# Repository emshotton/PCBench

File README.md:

# PCBench: A Dataset for Printed Circuit Board Routing
PCBench is a dataset for PCB routing task, it includes a dataset consisting of 164 printed circuit boards (PCB), a data augmentation script  to expand the dataset for supervised learning (SL) tasks, and a reinforcement learning (RL) environment.

## Dataset
### Folder Structure
All the PCB designs in our dataset are stored in the folder `PCBs`, where each PCB design is stored in a subfolder named `{author/org}_{PCB_name}_{design_version(optional)}`. Below is the folder structure of the dataset.
```
├── PCBs
│   ├── master_metadata.json
│   ├── subfolder1
│   │   ├── raw.kicad_pcb
│   │   ├── processed.kicad_pcb
│   │   ├── final.json
│   │   ├── metadata.json
│   │   ├── visual.png
│   ├── subfolder2
│   │   ├── raw.kicad_pcb
│   │   ├── processed.kicad_pcb
│   │   ├── final.json
│   │   ├── metadata.json
│   │   ├── visual.png
│   ├── ...
```
The `raw.kicad_pcb` is the raw PCB design file, `process.kicad_pcb` is the file after cleaning up, `final.json` stores only  routing-related information used for ML tasks. `metadata.json` stores the meta information for each single PCB design. `visual.png` is a visualization of each single PCB design. `master_meta.json` contains metadata of all PCBs and global-level information.

### PCB Routing Description Language (PCB-RDL)
We propose a JSON specification (`final.json` for each PCB design) called the PCB Routing Description  Language (PCB-RDL) that expresses a PCB routing problem and its solutions intuitively using basic concepts in order to facilitate research into automated PCB routing using ML. Following figure shows is an example of PCB with marked components in PCB-RDL (Left) and it corrsponding PCB-RDL (Right).

## Data Augmentation
### Run
The augmentation data can be generated with the script [`Scripts/Data_augmentation/augmentation.py`](https://github.com/PCBench/PCBench/blob/main/Scripts/Data_augmentation/augmentation.py).  To generate 3 samples by randomly extracting 50% nets from the PCB `1Bitsy_1bitsy`, please run the following command
```
cd Scripts/Data_augmentation/
python augmentation.py --num_samples 3 --net_ratio 0.5 --pcb_name 1Bitsy_1bitsy
```
### Output
All the generated PCBs will be stored in the folder named `augmented_data` under  `Scripts/Data_augmentation/`. In `augmented_data`, all the generated samples will be stored in a subfolder with the name of selected PCB. Each generated sample has the name `sample_index.json`. For example, the above command will generate the following file under `Scripts/Data_augmentation/`
```
├── augmented_data
│   ├── 1Bitsy_1bitsy
│   │   ├── 1.json
│   │   ├── 2.json
│   │   ├── 3.json
```

## RL environment

### Installation
The RL environment requires Python >= 3.7. You can simply install the environment with the following commands:
```
git clone https://github.com/PCBench/PCBench.git
cd PCBench
python setup.py install
```
After installation, open a Python console and type
```
from RLEnv.EnvLayer.PCBRoutingEnv import PCBRoutingEnv
```
If no error occurs, you have successfully installed the PCB routing environment.

### API Usage
The following content shows an example of API usage of PCBRoutingEnv. 
```
from RLEnv.EnvLayer.PCBRoutingEnv import PCBRoutingEnv
import random

resolution = [0.5, 0.5]
pcb_folder = '../PCBs/'
pcb_names = ["1Bitsy_1bitsy"]
iters = 30
env = PCBRoutingEnv(resolution=resolution, pcb_folder=pcb_folder, pcb_names=pcb_names)
obs, info = env.reset()
for _ in range(iters):
    act = random.randint(0,5)
    obs, rew, terminal, _, info = env.step(act)
    if terminal:
        env.reset()
```
You can find more examples of customizing functions of reward and state observation from [RLEnv/examples.ipynb](https://github.com/PCBench/PCBench/blob/main/RLEnv/examples.ipynb).

## Licensing

The code in this repository (scripts, the RL environment, notebooks) is released under the
MIT license in [`LICENSE`](LICENSE). **The boards under `PCBs/` are not.** Each board keeps
the license its authors chose, and each board folder records it:

- `metadata.json` → `licenses` holds the SPDX id, the license file's path in the source
  repository, the source commit the board was taken from, and a `status`:
  `licensed`, `licensed-unclassified` (a license file exists but could not be reduced to one
  SPDX id; read it), `unlicensed` (the source publishes no license), or `source-missing`
  (the source repository has since been deleted).
- `LICENSE` is the license text copied verbatim from the source repository.
- `NOTICE.md` carries the attribution (author, source, commit, retrieval date) and the
  modification statement required by CERN-OHL, the GPL family and the Creative Commons
  licenses: `processed.kicad_pcb` and `final.json` are derived from `raw.kicad_pcb` and stay
  under the source license.

Boards marked `unlicensed` are held for research and evaluation only. Their authors retain
all rights, and they must not be redistributed; [`LICENSES.md`](LICENSES.md) lists them
along with counts per license. `Scripts/Licensing/resolve_licenses.py` regenerates all of
the above from the source repositories.

### Boards added after the original collection

Boards added with `Scripts/Data_collection/add_boards.py` (their `metadata.json` carries
`source_path` and `source_commit`) differ from the original 1182 in two ways:
`processed.kicad_pcb` is the raw board with zone fills removed and routing kept, rather than
the re-routed board of the original cleaning pipeline; and `final.json`/`visual.png` are not
present, because the PCB-RDL extractor handles the KiCad 5 file format only.

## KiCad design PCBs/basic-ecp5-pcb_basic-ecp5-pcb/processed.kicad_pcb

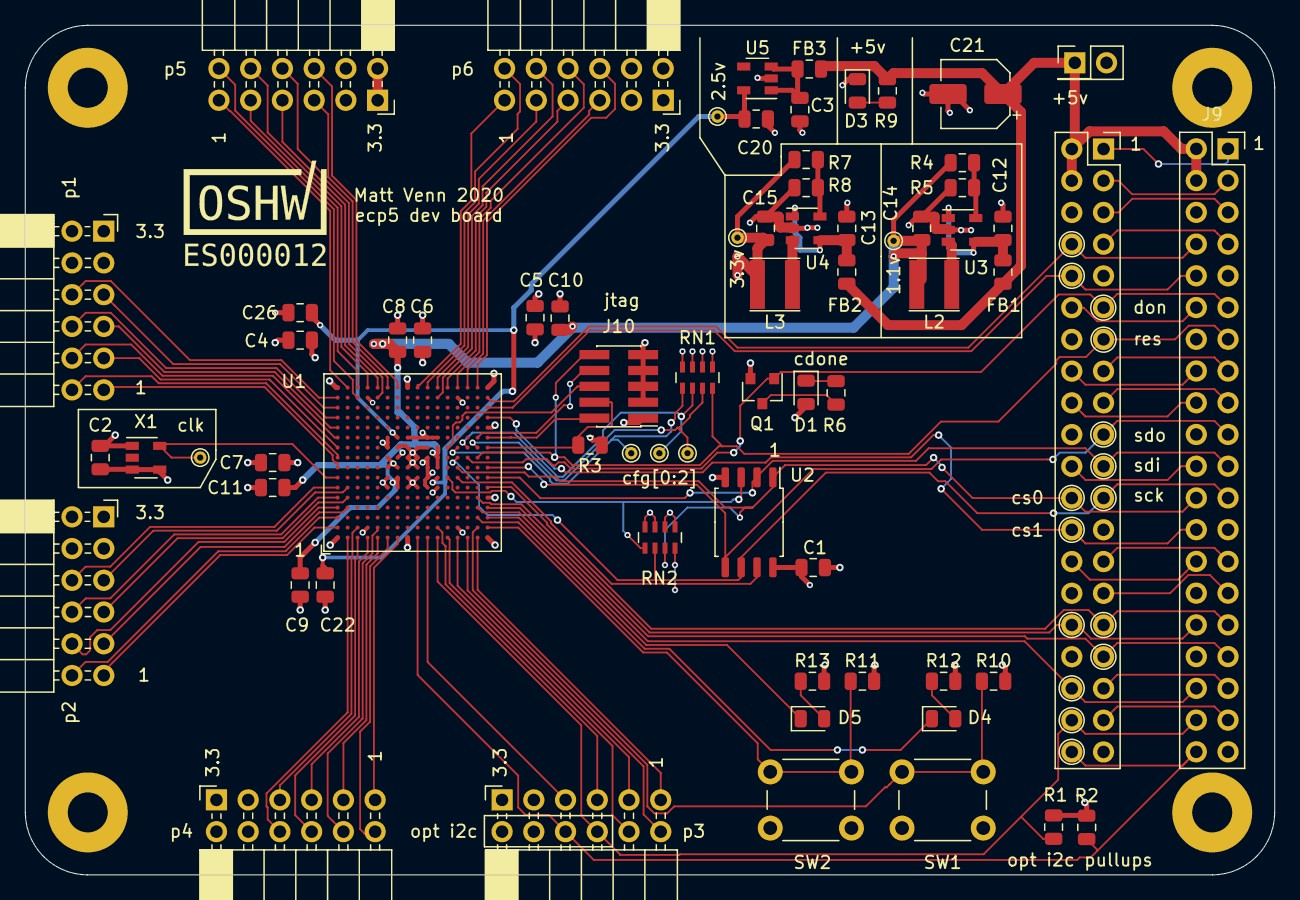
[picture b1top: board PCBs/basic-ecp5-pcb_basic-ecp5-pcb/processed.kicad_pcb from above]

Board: 4 copper layers, 100.0 x 68.0 mm, 73 parts (0 on the bottom side), 107 nets.

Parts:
C1, C2, C4, C5, C6, C8, C9, C10, C22: 100n; C_0805_2012Metric
C3, C20: 1u; C_0805_2012Metric
C7, C11, C15, C26: 10u; C_0805_2012Metric
C12, C13: 4.7u; C_0805_2012Metric
C14: 22u; C_0805_2012Metric
C21: CP; CP_Elec_5x5.4
D1, D3, D4, D5: LED; LED_0805_2012Metric
FB1, FB2, FB3: Ferrite_Bead_Small; L_0805_2012Metric
H1, H2, H3, H4: MountingHole_Pad; MountingHole_3.2mm_M3_Pad
J1: Conn_01x02; PinHeader_2x01_P2.54mm_Vertical
J2, J9: Conn_02x20_Odd_Even; PinSocket_2x20_P2.54mm_Vertical
J3, J4, J5, J6, J7, J8: Conn_02x06_Odd_Even; PinSocket_2x06_P2.54mm_Horizontal
J10: Conn_02x05_Odd_Even; PinHeader_2x05_P1.27mm_Vertical_SMD
L2, L3: 2.2uH; L_Taiyo-Yuden_NR-40xx
Q1: Q_NMOS_GSD; SOT-23
R1, R2, R3, R10, R11: 10k; R_0805_2012Metric
R4: 100k; R_0805_2012Metric
R5: 120k; R_0805_2012Metric
R6, R9, R12, R13: 200R; R_0805_2012Metric
R7: 68k; R_0805_2012Metric
R8: 15k; R_0805_2012Metric
RN1, RN2: 10k; R_Array_Concave_4x0603
SW1, SW2: SW_Push; SW_PUSH_6mm
TP1: 3.3v; TestPoint_THTPad_D1.0mm_Drill0.5mm
TP2, TP4, TP7: TestPoint; TestPoint_THTPad_D1.0mm_Drill0.5mm
TP3: 2.5v; TestPoint_THTPad_D1.0mm_Drill0.5mm
TP5: clock; TestPoint_THTPad_D1.0mm_Drill0.5mm
TP6: 1.1v; TestPoint_THTPad_D1.0mm_Drill0.5mm
U1: ECP5U_45_CABGA256; BGA-256_14.0x14.0mm_Layout16x16_P0.8mm_Ball0.45mm_Pad0.32mm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
U2: IS25LP016D-JBLE; SOIC-8_5.23x5.23mm_P1.27mm
U3, U4: TLV62568DBV; SOT-23-5
U5: TLV73325PDBV; SOT-23-5
X1: SiT2001B; SOT-23-5

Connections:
+1V1: C8.1, C9.1, C10.1, C11.1, C14.1, L2.2, R4.2, TP6.1, U1.G6, U1.G7, U1.G9, U1.L8, U1.L9, U1.L10
+2V5: C20.1, C22.1, C26.1, TP3.1, U1.G11, U1.L7, U5.5
+3.3VP: C1.1, C2.1, C4.1, C5.1, C6.1, C7.1, C15.1, D1.2, J3.1, J3.2, J4.1, J4.2, J5.1, J5.2, J6.1, J6.2, J7.1, J7.2, J8.1, J8.2, J10.1, L3.2, R1.1, R2.1, R7.2, R10.2, R11.2, R12.2, R13.2, RN1.5, RN1.7, RN2.5, RN2.6, RN2.7, RN2.8, TP1.1, U1.F6, U1.F7, U1.F10, U1.F11, U1.H6, U1.H7, U1.H11, U1.J6, U1.J7, U1.J11, U1.K11, U1.L6, U1.L11, U2.8, X1.3, X1.4
+5V: C21.1, FB1.2, FB2.2, FB3.2, J1.1, J2.2, J2.4, J9.2, J9.4, R9.2
/fpga/cfg_0: RN1.1, TP2.1, U1.N10
/fpga/cfg_1: RN1.2, TP4.1, U1.P10
/fpga/cfg_2: RN1.3, TP7.1, U1.R10
/fpga/tck: J10.4, R3.2, U1.T10
/fpga/tdi: J10.8, U1.R11
/fpga/tdo: J10.6, U1.M10
/fpga/tms: J10.2, U1.T11
/gp0: J2.27, J9.27
/gp1: J2.28, J9.28
/gp2: J2.3, J9.3
/gp3: J2.5, J9.5
/gp4: J2.7, J9.7
/gp5: J2.29, J9.29
/gp18: J2.12, J9.12
/gp19: J2.35, J9.35
/gp22: J2.15, J9.15
/gp23: J2.16, J9.16
/gp24: J2.18, J9.18
/gp25: J2.22, J9.22
/gp26: J2.37, J9.37
/pi_3v3: J2.1, J9.1
/pi_3v3_2: J2.17, J9.17
GND: C1.2, C2.2, C3.2, C4.2, C5.2, C6.2, C7.2, C8.2, C9.2, C10.2, C11.2, C12.2, C13.2, C14.2, C15.2, C20.2, C21.2, C22.2, C26.2, D3.1, H1.1, H2.1, H3.1, H4.1, J1.2, J2.6, J2.9, J2.14, J2.20, J2.25, J2.30, J2.34, J2.39, J3.3, J3.4, J4.3, J4.4, J5.3, J5.4, J6.3, J6.4, J7.3, J7.4, J8.3, J8.4, J9.6, J9.9, J9.14, J9.20, J9.25, J9.30, J9.34, J9.39, J10.3, J10.5, J10.7, J10.9, Q1.2, R3.1, R5.1, R8.1, RN1.6, RN1.8, SW1.2, SW2.2, U1.A1, U1.A16, U1.D2, U1.D15, U1.F8, U1.F9, U1.G8, U1.G10, U1.H1, U1.H8, U1.H9, U1.H10, U1.H16, U1.J8, U1.J9, U1.J10, U1.K6, U1.K7, U1.K8, U1.K9, U1.K10, U1.N2, U1.N15, U1.T1, U1.T5, U1.T12, U1.T16, U2.4, U3.2, U4.2, U5.2, X1.1
unnamed: C3.1, FB3.1, U5.1, U5.3
unnamed: C12.1, FB1.1, U3.1, U3.4
unnamed: C13.1, FB2.1, U4.1, U4.4
unnamed: D1.1, R6.1
unnamed: D3.2, R9.1
unnamed: D4.2, R12.1
unnamed: D5.2, R13.1
unnamed: L2.1, U3.3
unnamed: L3.1, U4.3
unnamed: Q1.3, R6.2
unnamed: R4.1, R5.2, U3.5
unnamed: R7.1, R8.2, U4.5
button1: R10.1, SW1.1, U1.R2
button2: R11.1, SW2.1, U1.T2
cdone: J2.11, J9.11, Q1.1, U1.P9
ce1: J2.26, J9.26, U1.T13
clk: TP5.1, U1.A7, X1.5
creset: J2.13, J9.13, J10.10, RN1.4, U1.R9
gp6: J2.31, J9.31, U1.T6
gp12: J2.32, J9.32, U1.R5
gp13: J2.33, J9.33, U1.T4
gp14: J2.8, J9.8, U1.T15
gp15: J2.10, J9.10, U1.T14
gp16: J2.36, J9.36, U1.R4
led1: D4.1, U1.R3
led2: D5.1, U1.T3
p1_1: J3.11, U1.A8
p1_2: J3.9, U1.A10
p1_3: J3.7, U1.A12
p1_4: J3.5, U1.A14
p1_7: J3.12, U1.A9
p1_8: J3.10, U1.A11
p1_9: J3.8, U1.A13
p1_10: J3.6, U1.A15
p2_1: J4.11, U1.A2
p2_2: J4.9, U1.B4
p2_3: J4.7, U1.B5
p2_4: J4.5, U1.B6
p2_7: J4.12, U1.A3
p2_8: J4.10, U1.A4
p2_9: J4.8, U1.A5
p2_10: J4.6, U1.A6
p3_1: J5.11, U1.R1
p3_2: J5.9, U1.N1
p3_3: J5.7, U1.L2
p3_4: J5.5, U1.K1
p3_7: J5.12, U1.P1
p3_8: J5.10, U1.M1
p3_9: J2.38, J5.8, J9.38, R1.2, U1.L1
p3_10: J2.40, J5.6, J9.40, R2.2, U1.J1
p4_1: J6.11, U1.G1
p4_2: J6.9, U1.E1
p4_3: J6.7, U1.D1
p4_4: J6.5, U1.C2
p4_7: J6.12, U1.F1
p4_8: J6.10, U1.E2
p4_9: J6.8, U1.C1
p4_10: J6.6, U1.B1
p5_1: J7.11, U1.B16
p5_2: J7.9, U1.C16
p5_3: J7.7, U1.E16
p5_4: J7.5, U1.F16
p5_7: J7.12, U1.C15
p5_8: J7.10, U1.D16
p5_9: J7.8, U1.E15
p5_10: J7.6, U1.G16
p6_1: J8.11, U1.J16
p6_2: J8.9, U1.L16
p6_3: J8.7, U1.M16
p6_4: J8.5, U1.P16
p6_7: J8.12, U1.K16
p6_8: J8.10, U1.L15
p6_9: J8.8, U1.N16
p6_10: J8.6, U1.R16
sd_clk: J2.23, J9.23, RN2.2, U1.N9, U2.6
sd_cs: J2.24, J9.24, RN2.3, U1.N8, U2.1
sd_io2: RN2.1, U1.M7, U2.3
sd_io3: RN2.4, U1.N7, U2.7
sdi: J2.21, J9.21, U1.T7, U2.2
sdo: J2.19, J9.19, U1.T8, U2.5

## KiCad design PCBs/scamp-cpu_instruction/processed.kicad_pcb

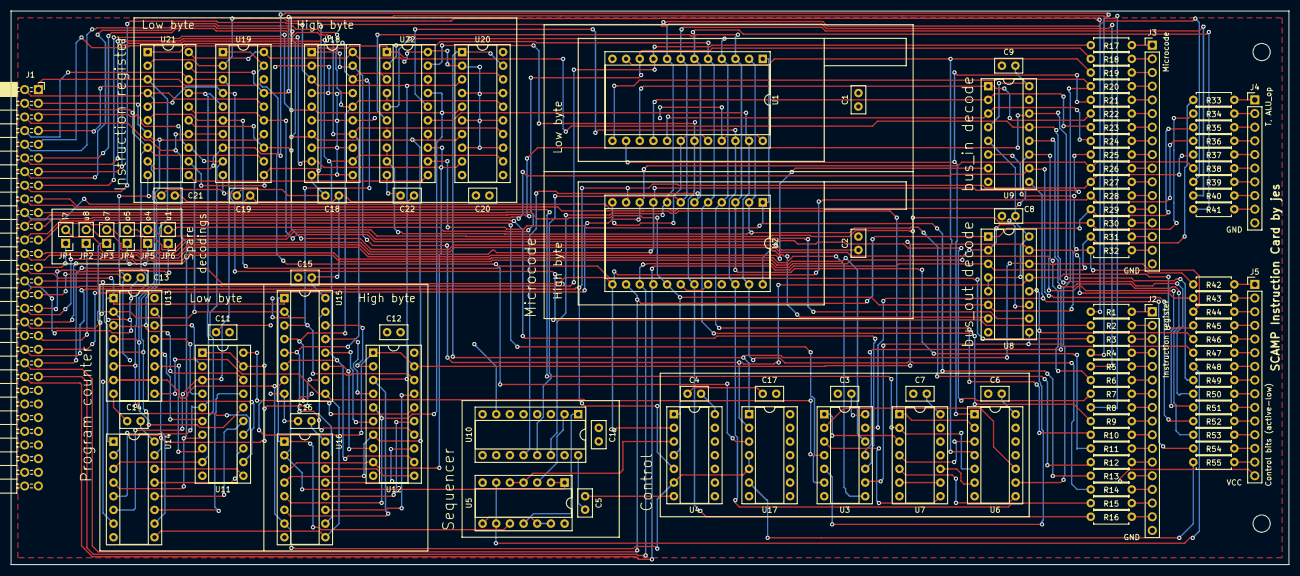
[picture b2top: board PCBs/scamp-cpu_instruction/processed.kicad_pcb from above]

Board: 2 copper layers, 237.5 x 102.9 mm, 110 parts (0 on the bottom side), 172 nets.

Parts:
C1, C2, C3, C4, C5, C6, C7, C8, C9, C10, C11, C12, C13, C14, C15, C16, C17, C18, C19, C20, C21, C22: C; C_Disc_D5.0mm_W2.5mm_P2.50mm
J1: Conn_02x30_Counter_Clockwise; PinSocket_2x30_P2.54mm_Horizontal
J2, J3: Conn_01x17_Male; PinHeader_1x17_P2.54mm_Vertical
J4: Conn_01x10_Male; PinHeader_1x10_P2.54mm_Vertical
J5: Conn_01x15_Male; PinHeader_1x15_P2.54mm_Vertical
JP1, JP2, JP3, JP4, JP5, JP6: Jumper_NO_Small; PinHeader_1x02_P2.54mm_Vertical
R1, R2, R3, R4, R5, R6, R7, R8, R9, R10, R11, R12, R13, R14, R15, R16, R17, R18, R19, R20, R21, R22, R23, R24, R25, R26, R27, R28, R29, R30, R31, R32, R33, R34, R35, R36, R37, R38, R39, R40, R41, R42, R43, R44, R45, R46, R47, R48, R49, R50, R51, R52, R53, R54, R55: R; R_Axial_DIN0207_L6.3mm_D2.5mm_P7.62mm_Horizontal
U1, U2: 28C16; DIP-24_W15.24mm_Socket
U3: 74LS04; DIP-14_W7.62mm_Socket
U4, U6: 74LS08; DIP-14_W7.62mm_Socket
U5, U17: 74LS00; DIP-14_W7.62mm_Socket
U7: 74LS32; DIP-14_W7.62mm_Socket
U8, U9: 74LS138; DIP-16_W7.62mm_Socket
U10, U13, U14, U15, U16: 74LS161; DIP-16_W7.62mm_Socket
U11, U12, U18, U19, U20: 74LS244; DIP-20_W7.62mm_Socket
U21, U22: 74LS377; DIP-20_W7.62mm_Socket

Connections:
CLK: J1.29, U5.1, U5.2, U13.2, U14.2, U15.2, U16.2, U21.11, U22.11
D0: J1.1, U11.18, U13.3, U19.18, U21.3
D1: J1.2, U11.16, U13.4, U19.16, U21.4
D2: J1.3, U11.14, U13.5, U19.14, U21.7
D3: J1.4, U11.12, U13.6, U19.12, U21.8
D4: J1.5, U11.9, U14.3, U19.9, U21.13
D5: J1.6, U11.7, U14.4, U19.7, U21.14
D6: J1.7, U11.5, U14.5, U19.5, U21.17
D7: J1.8, U11.3, U14.6, U19.3, U21.18
D8: J1.9, U12.18, U15.3, U18.18, U20.18, U22.3
D9: J1.10, U12.16, U15.4, U18.16, U20.16, U22.4
D10: J1.11, U12.14, U15.5, U18.14, U20.14, U22.7
D11: J1.12, U12.12, U15.6, U18.12, U20.12, U22.8
D12: J1.13, U12.9, U16.3, U18.9, U20.9, U22.13
D13: J1.14, U12.7, U16.4, U18.7, U20.7, U22.14
D14: J1.15, U12.5, U16.5, U18.5, U20.5, U22.17
D15: J1.16, U12.3, U16.6, U18.3, U20.3, U22.18
DI: J1.26, U3.12
DO: J1.25, U3.8
EX: J1.44, R31.1, R33.1, U2.16, U8.3
EY: J1.42, R29.1, R35.1, U2.14, U8.1
F: J1.40, R27.1, R37.1, U2.11, U4.5
GND: C1.2, C2.2, C3.2, C4.2, C5.2, C6.2, C7.2, C8.2, C9.2, C10.2, C11.2, C12.2, C13.2, C14.2, C15.2, C16.2, C17.2, C18.2, C19.2, C20.2, C21.2, C22.2, J1.31, J2.17, J3.17, J4.10, U1.12, U1.18, U1.20, U2.12, U2.18, U2.20, U3.7, U4.7, U5.7, U6.7, U7.7, U8.8, U9.8, U10.8, U11.10, U12.10, U13.8, U14.8, U15.8, U16.8, U17.7, U18.2, U18.4, U18.6, U18.8, U18.10, U18.11, U18.13, U18.15, U18.17, U19.10, U20.10, U21.10, U22.10
GT: U3.2, U6.10
I0: R1.1, U19.2, U21.2
I1: R2.1, U19.4, U21.5
I2: R3.1, U19.6, U21.6
I3: R4.1, U19.8, U21.9
I4: R5.1, U19.11, U21.12
I5: R6.1, U19.13, U21.15
I6: R7.1, U19.15, U21.16
I7: R8.1, U19.17, U21.19
I8: R9.1, U1.5, U2.5, U22.2
I9: R10.1, U1.4, U2.4, U22.5
I10: R11.1, U1.3, U2.3, U22.6
I11: R12.1, U1.2, U2.2, U22.9
I12: R13.1, U1.1, U2.1, U22.12
I13: R14.1, U1.23, U2.23, U22.15
I14: R15.1, U1.22, U2.22, U22.16
I15: R16.1, U1.19, U2.19, U22.19
JGT: R20.1, U1.13, U6.9
JGT_GT: U6.8, U7.5
JLT: R19.1, U1.11, U6.4
JLT_LT: U6.6, U7.10
JMP: U3.3, U7.8
JZ: R21.1, U1.14, U6.1
JZ_Z: U6.3, U7.4
LT: J1.18, U6.5, U7.2
MI: J1.24, U3.10
MO: J1.23, U3.6
NO: J1.39, R26.1, R38.1, U2.10
NX: J1.43, R30.1, R34.1, U2.15, U8.2
NY: J1.41, R28.1, R36.1, U2.13, U4.2
unnamed: J1.27, JP1.1
unnamed: J1.33, JP6.1
unnamed: J1.34, JP5.1
unnamed: J1.35, JP4.1
unnamed: J1.36, JP3.1
unnamed: J1.37, JP2.1
unnamed: J2.1, R1.2
unnamed: J2.2, R2.2
unnamed: J2.3, R3.2
unnamed: J2.4, R4.2
unnamed: J2.5, R5.2
unnamed: J2.6, R6.2
unnamed: J2.7, R7.2
unnamed: J2.8, R8.2
unnamed: J2.9, R9.2
unnamed: J2.10, R10.2
unnamed: J2.11, R11.2
unnamed: J2.12, R12.2
unnamed: J2.13, R13.2
unnamed: J2.14, R14.2
unnamed: J2.15, R15.2
unnamed: J2.16, R16.2
unnamed: J3.1, R17.2
unnamed: J3.2, R18.2
unnamed: J3.3, R19.2
unnamed: J3.4, R20.2
unnamed: J3.5, R21.2
unnamed: J3.6, R22.2
unnamed: J3.7, R23.2
unnamed: J3.8, R24.2
unnamed: J3.9, R25.2
unnamed: J3.10, R26.2
unnamed: J3.11, R27.2
unnamed: J3.12, R28.2
unnamed: J3.13, R29.2
unnamed: J3.14, R30.2
unnamed: J3.15, R31.2
unnamed: J3.16, R32.2
unnamed: J4.1, R33.2
unnamed: J4.2, R34.2
unnamed: J4.3, R35.2
unnamed: J4.4, R36.2
unnamed: J4.5, R37.2
unnamed: J4.6, R38.2
unnamed: J4.7, R39.2
unnamed: J4.8, R40.2
unnamed: J4.9, R41.2
unnamed: J5.1, R42.2
unnamed: J5.2, R43.2
unnamed: J5.3, R44.2
unnamed: J5.4, R45.2
unnamed: J5.5, R46.2
unnamed: J5.6, R47.2
unnamed: J5.7, R48.2
unnamed: J5.8, R49.2
unnamed: J5.9, R50.2
unnamed: J5.10, R51.2
unnamed: J5.11, R52.2
unnamed: J5.12, R53.2
unnamed: J5.13, R54.2
unnamed: J5.14, R55.2
unnamed: U5.8, U5.12, U5.13
unnamed: U7.6, U7.9
unnamed: U13.15, U14.10
unnamed: U14.15, U15.10
unnamed: U15.15, U16.10
P0: U11.2, U13.14
P1: U11.4, U13.13
P2: U11.6, U13.12
P3: U11.8, U13.11
P4: U11.11, U14.14
P5: U11.13, U14.13
P6: U11.15, U14.12
P7: U11.17, U14.11
P8: U12.2, U15.14
P9: U12.4, U15.13
P10: U12.6, U15.12
P11: U12.8, U15.11
P12: U12.11, U16.14
P13: U12.13, U16.13
P14: U12.15, U16.12
P15: U12.17, U16.11
PP: U4.6, U13.7, U13.10, U14.7, U15.7, U16.7, U17.4, U17.5
RT: U4.3, U5.4, U5.5
T0: R39.1, U1.8, U2.8, U10.14
T1: R40.1, U1.7, U2.7, U10.13
T2: R41.1, U1.6, U2.6, U10.12
U0: J1.32, R17.1, U1.9
U1: JP6.2, R18.1, U1.10
U5: R22.1, U1.15, U9.1
U6: R23.1, U1.16, U9.2
U7: R24.1, U1.17, U9.3
U8: JP2.2, R25.1, U2.9
U15: J1.19, R32.1, R42.1, U2.17, U4.1, U4.4, U8.6, U9.6
VCC: C1.1, C2.1, C3.1, C4.1, C5.1, C6.1, C7.1, C8.1, C9.1, C10.1, C11.1, C12.1, C13.1, C14.1, C15.1, C16.1, C17.1, C18.1, C19.1, C20.1, C21.1, C22.1, J1.30, J5.15, U1.21, U1.24, U2.21, U2.24, U3.14, U4.14, U5.14, U6.14, U7.14, U8.4, U8.5, U8.16, U9.4, U9.5, U9.16, U10.7, U10.9, U10.10, U10.16, U11.20, U12.20, U13.16, U14.16, U15.16, U16.16, U17.14, U18.20, U19.20, U20.2, U20.4, U20.6, U20.8, U20.11, U20.13, U20.15, U20.17, U20.20, U21.20, U22.20
Z: J1.17, U6.2, U7.1
Z_LT: U3.1, U7.3
inv_CLK: U5.3, U10.2
inv_DI: R54.1, U3.13, U9.9
inv_DO: R47.1, U3.9, U8.9
inv_MI: R53.1, U3.11, U9.12
inv_MO: R46.1, U3.5, U8.12
inv_PP: R55.1, U17.6
inv_RT: R48.1, U5.6, U5.9
spare_I7: JP1.2, U9.7
spare_O4: JP5.2, U8.11
spare_O5: JP4.2, U8.10
spare_O7: JP3.2, U8.7
~AI~: J1.22, R49.1, U9.14
~II~: R50.1, U9.13, U21.1, U22.1
~IOH~: R44.1, U8.14, U17.1, U20.1, U20.19
~IOLH~: U17.3, U19.1, U19.19
~IOL~: R45.1, U8.13, U17.2, U18.1, U18.19
~JMP~: U3.4, U13.9, U14.9, U15.9, U16.9
~PO~: R43.1, U8.15, U11.1, U11.19, U12.1, U12.19
~RESET~: J1.28, U5.10, U13.1, U14.1, U15.1, U16.1
~XI~: J1.20, R51.1, U9.11
~YI~: J1.21, R52.1, U9.10
~reset_T~: U5.11, U10.1

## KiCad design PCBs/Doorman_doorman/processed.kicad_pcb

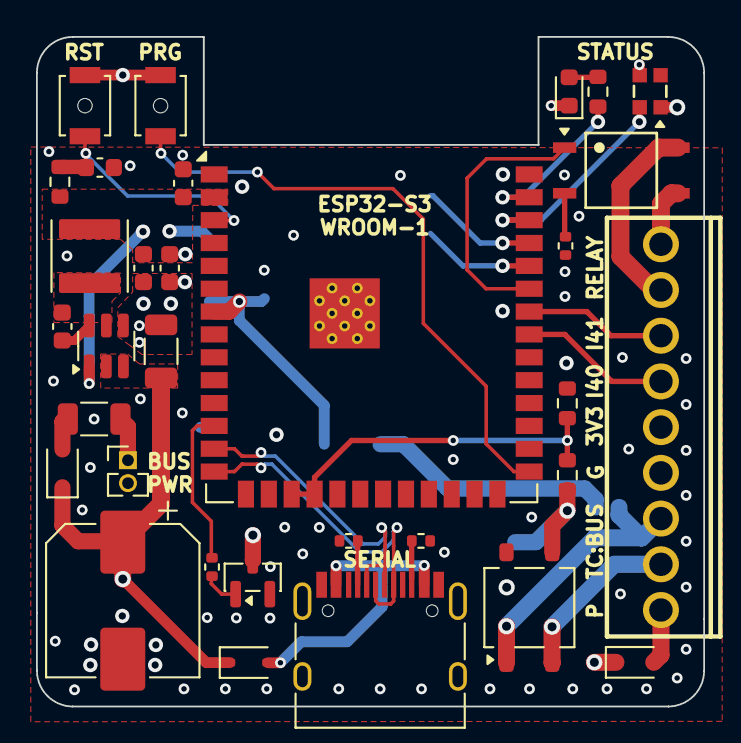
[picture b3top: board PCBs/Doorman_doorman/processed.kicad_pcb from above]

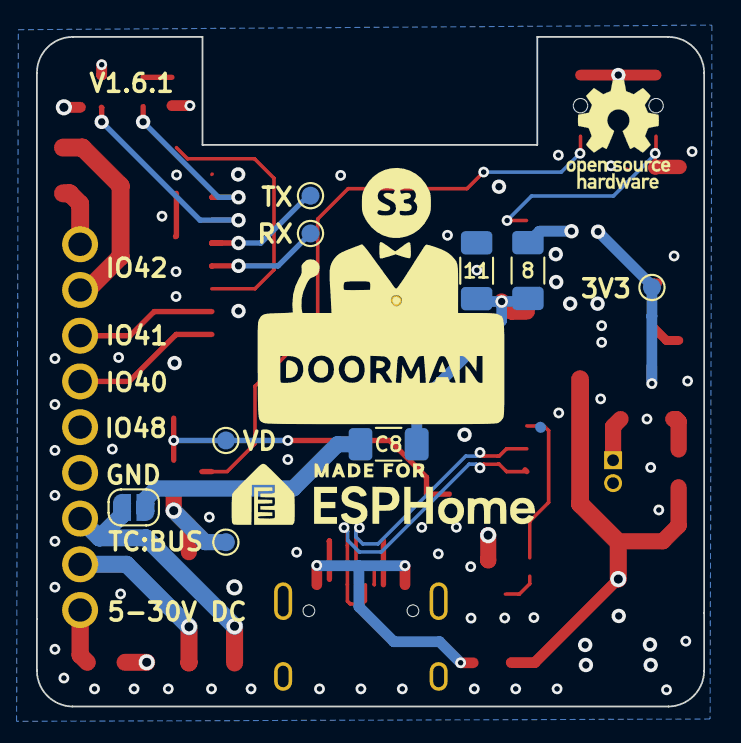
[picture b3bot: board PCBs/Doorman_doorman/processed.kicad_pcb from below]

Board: 4 copper layers, 37.1 x 37.2 mm, 41 parts (9 on the bottom side), 34 nets.

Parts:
8, 11: 10K; R_1206_3216Metric_Pad1.30x1.75mm_HandSolder
C1, C2, C5: 100nF; C_0603_1608Metric
C3: 470uF; CP_Elec_8x10
C4: 10uF; C_1206_3216Metric
C6, C7: 22uF; C_0603_1608Metric
C8: 33uF; C_1206_3216Metric_Pad1.33x1.80mm_HandSolder
D1, D5, D6: 1N5819WS; D_SOD-323
D2: MB6S; TO-269AA
D3: WS2812B; LED-SMD_4P-L2.0-W1.8_CY-0807
D4: Red; LED_0603_1608Metric
J1: USB_C_Receptacle_USB2.0; USB_C_Receptacle_HRO_TYPE-C-31-M-12
J2: Terminal; CONN-TH_9P-P2.54_KF128-2.54-9P
J3: 3V3 Test Pad; TestPoint_Pad_D1.0mm
J4: TX Test Pad; TestPoint_Pad_D1.0mm
J5: RX Test Pad; TestPoint_Pad_D1.0mm
J6: BUS Test Pad; TestPoint_Pad_D1.0mm
J7: BUS RX Test Pad; TestPoint_Pad_D1.0mm
JP1: Bus power Jumper; PinHeader_1x02_P1.27mm_Vertical
JP2: SolderJumper_2_Open; SolderJumper-2_P1.3mm_Open_RoundedPad1.0x1.5mm
L1: 3.9uH; L_Abracon_ASPI-4030S
Q1: BC817; SOT-23
R1: 10K; R_0603_1608Metric
R2: 1K; R_0402_1005Metric
R3, R4: 5.1K; R_0402_1005Metric
R5: 1M; R_0603_1608Metric
R6: 147K; R_0603_1608Metric
R7: 470; R_0603_1608Metric
R9: 150; R_0402_1005Metric
R10: 62; R_1206_3216Metric
SW1: Reset Button; SW_SPST_B3U-1000P-B
SW2: Flash Button; SW_SPST_B3U-1000P-B
U1: ESP32-S3-WROOM-1
U2: AP63203WU; TSOT-23-6
U3: GAQY252G3S; SOP-4_L4.4-W4.0-P2.54-LS7.0-TL

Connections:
+3.3V: 8.1, C2.2, C6.1, C7.1, D3.1 (VDD), J2.5, J3.1, L1.2, R1.1, U1.2 (3V3), U2.1 (FB)
+5V: D1.2 (A), J1.A4 (VBUS), J1.A9 (VBUS), J1.B4 (VBUS), J1.B9 (VBUS)
+24V Bus: D2.3 (+), J6.1, JP1.2 (B), Q1.3 (C), R5.1
/EN: C1.1, R1.2, SW1.1, U1.3 (EN)
/FLASH: SW2.1, U1.27 (IO0)
/RXD: J5.1, U1.36 (RXD0)
/TXD: J4.1, U1.37 (TXD0)
ADC_IN: 8.2, 11.2, C8.2, U1.7 (IO7)
BUS_ANA: J7.1, R5.2, R6.1, U1.17 (IO9), U1.18 (IO10)
BUS_TX: R2.2, U1.12 (IO8)
BUS_WIRE1: D2.1, J2.3, JP2.1 (A)
BUS_WIRE2: D2.2, J2.2
GND: 11.1, C1.2, C2.1, C3.2, C4.2, C6.2, C7.2, D2.4 (-), D3.3 (GND), D4.1 (K), J1.A1 (GND), J1.A12 (GND), J1.B1 (GND), J1.B12 (GND), J1.S1 (SHIELD), J2.4, Q1.2 (E), R3.2, R4.1, R6.2, R9.2, SW1.2, SW2.2, U1.1 (GND), U1.40 (GND), U1.41 (GND), U2.4 (GND)
IO40: J2.6, U1.33 (IO40)
IO41: J2.7, U1.34 (IO41)
LED_RED: R7.1, U1.39 (IO1)
LED_RGB: D3.4 (DIN), U1.38 (IO2)
unnamed: C3.1, C4.1, D1.1 (K), D5.1 (K), D6.1 (K), U2.2 (EN), U2.3 (IN)
unnamed: D4.2 (A), R7.2
unnamed: D6.2 (A), R10.1
unnamed: J1.A5 (CC1), R3.1
unnamed: J1.B5 (CC2), R4.2
unnamed: JP1.1 (A), R10.2
unnamed: C8.1, JP2.2 (B)
unnamed: Q1.1 (B), R2.1
unnamed: R9.1, U3.2
unnamed: C5.1, U2.6 (BST)
unnamed: C5.2, L1.1, U2.5 (SW)
RELAY_WIRE1: J2.9, U3.3
RELAY_WIRE2: J2.8, U3.4
SSR: U1.35 (IO42), U3.1
USB_D+: J1.A6 (D+), J1.B6 (D+), U1.14 (IO20)
USB_D-: J1.A7 (D-), J1.B7 (D-), U1.13 (IO19)
VCC: D5.2 (A), J2.1

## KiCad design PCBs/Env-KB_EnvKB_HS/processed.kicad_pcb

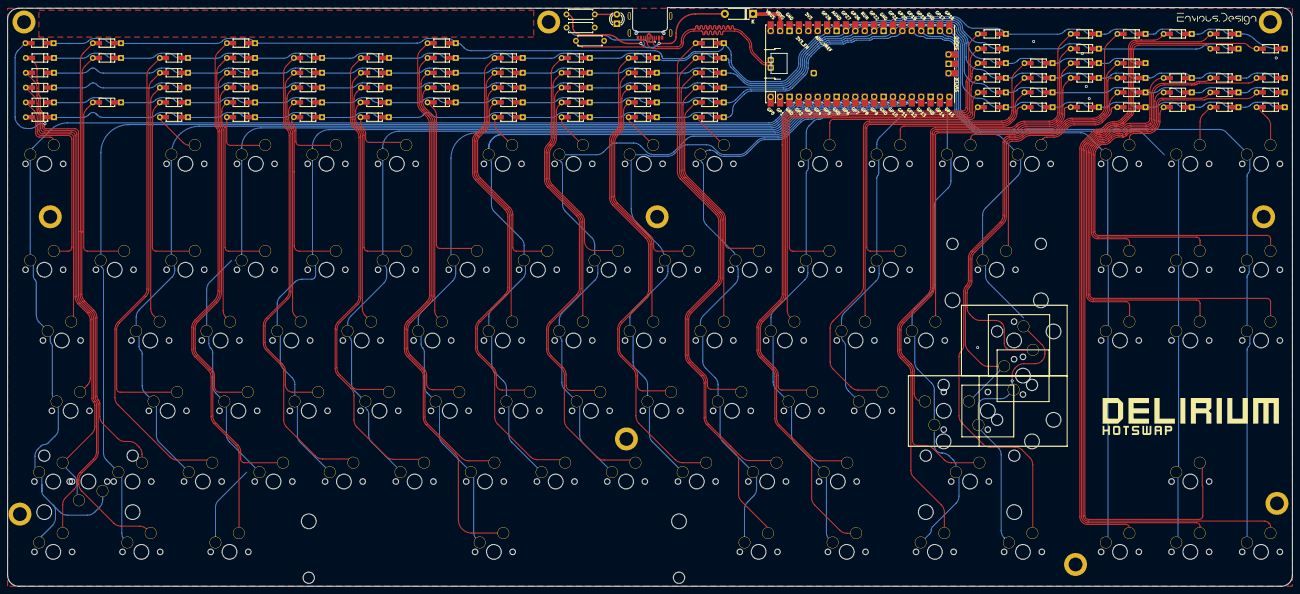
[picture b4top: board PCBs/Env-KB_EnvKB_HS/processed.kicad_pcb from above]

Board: 2 copper layers, 347.0 x 156.3 mm, 206 parts (0 on the bottom side), 121 nets.

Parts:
D0, D1, D2, D3, D4, D5, D6, D7, D8, D9, D10, D11, D12, D13, D14, D15, D16, D17, D18, D19, D20, D21, D22, D23, D24, D25, D26, D27, D28, D29, D30, D31, D32, D33, D34, D35, D36, D37, D38, D39, D40, D41, D42, D43, D44, D45, D46, D47, D48, D49, D50, D51, D52, D53, D54, D55, D56, D57, D58, D59, D60, D61, D62, D63, D64, D65, D66, D67, D68, D69, D70, D71, D72, D73, D74, D75, D76, D77, D78, D79, D80, D81, D82, D83, D84, D85, D86, D87, D88: D; SOD-123+D_DO-35_SOD27_P7.62mm_Horizontal
D89: 1n4002; D_DO-41_SOD81_P7.62mm_Horizontal
H0, H1, H2, H3, H4, H5, H6, H7, H9, H10: MountingHole; MountingHole_3.7mm_Pad
K_0, K_1, K_2, K_3, K_4, K_5, K_6, K_7, K_8, K_9, K_10, K_11, K_12, K_13, K_14, K_15, K_16, K_17, K_18, K_19, K_20, K_21, K_22, K_23, K_24, K_25, K_26, K_27, K_28, K_29, K_30, K_31, K_32, K_33, K_34, K_35, K_36, K_37, K_38, K_39, K_40, K_41, K_42, K_43, K_44, K_45, K_46, K_47, K_48, K_49, K_50, K_51, K_52, K_53, K_54, K_55, K_56, K_57, K_58, K_59, K_60, K_61, K_62, K_64, K_64B1, K_65, K_66, K_67, K_68, K_69, K_70, K_71, K_72, K_73, K_74, K_75, K_76, K_77, K_78, K_79, K_80, K_81, K_82, K_83, K_84, K_85, K_86, K_87, K_88: KEYSW; MXOnly-1U-Hotswap-Modified
K_63, K_63B1: MX-NoLED; MXOnly-1U-Hotswap-Modified
LEDRESISTOR1: 5.1kohm 1/4w; R_Axial_DIN0207_L6.3mm_D2.5mm_P7.62mm_Horizontal
PowerLED0: LED 3MM; LED_D3.0mm_FlatTop
RESISTOR0, RESISTOR1: 5.1kohm 1/4w; R_Axial_DIN0207_L6.3mm_D2.5mm_P7.62mm_Horizontal
RPI0: Pico; RPi_Pico_SMD_TH
Stab1: Stabilizer; Stabilizer_Cherry_MX_6.25u
Stab2, Stab3, Stab4, Stab5, Stab6: Stabilizer; Stabilizer_Cherry_MX_2u
USB1: TYPE-C-31-M-14; USB_C_TYPE-C-31-M-14
kibuzzard-62A4A5BB: G***; kibuzzard-62A4A5BB
kibuzzard-6298A001: G***; kibuzzard-6298A001
kibuzzard-6298A037: G***; kibuzzard-6298A037

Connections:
GND: H0.1, H1.1, H2.1, H3.1, H4.1, H5.1, H6.1, H7.1, H9.1, H10.1, PowerLED0.1 (K), RESISTOR0.2, RESISTOR1.1, RPI0.3 (GND), RPI0.8 (GND), RPI0.13 (GND), RPI0.18 (GND), RPI0.23 (GND), RPI0.28 (GND), RPI0.38 (GND), USB1.A1 (GND), USB1.A12 (GND), USB1.B1 (GND), USB1.B12 (GND), USB1.S1 (SHIELD)
unnamed: D0.2 (A), K_0.2 (ROW)
unnamed: D1.2 (A), K_1.2 (ROW)
unnamed: D2.2 (A), K_2.2 (ROW)
unnamed: D3.2 (A), K_3.2 (ROW)
unnamed: D4.2 (A), K_4.2 (ROW)
unnamed: D5.2 (A), K_5.2 (ROW)
unnamed: D6.2 (A), K_6.2 (ROW)
unnamed: D7.2 (A), K_7.2 (ROW)
unnamed: D8.2 (A), K_8.2 (ROW)
unnamed: D9.2 (A), K_9.2 (ROW)
unnamed: D10.2 (A), K_10.2 (ROW)
unnamed: D11.2 (A), K_11.2 (ROW)
unnamed: D12.2 (A), K_12.2 (ROW)
unnamed: D13.2 (A), K_13.2 (ROW)
unnamed: D14.2 (A), K_14.2 (ROW)
unnamed: D15.2 (A), K_15.2 (ROW)
unnamed: D16.2 (A), K_16.2 (ROW)
unnamed: D17.2 (A), K_17.2 (ROW)
unnamed: D18.2 (A), K_18.2 (ROW)
unnamed: D19.2 (A), K_19.2 (ROW)
unnamed: D20.2 (A), K_20.2 (ROW)
unnamed: D21.2 (A), K_21.2 (ROW)
unnamed: D22.2 (A), K_22.2 (ROW)
unnamed: D23.2 (A), K_23.2 (ROW)
unnamed: D24.2 (A), K_24.2 (ROW)
unnamed: D25.2 (A), K_25.2 (ROW)
unnamed: D26.2 (A), K_26.2 (ROW)
unnamed: D27.2 (A), K_27.2 (ROW)
unnamed: D28.2 (A), K_28.2 (ROW)
unnamed: D29.2 (A), K_29.2 (ROW)
unnamed: D30.2 (A), K_30.2 (ROW)
unnamed: D31.2 (A), K_31.2 (ROW)
unnamed: D32.2 (A), K_32.2 (ROW)
unnamed: D33.2 (A), K_33.2 (ROW)
unnamed: D34.2 (A), K_34.2 (ROW)
unnamed: D35.2 (A), K_35.2 (ROW)
unnamed: D36.2 (A), K_36.2 (ROW)
unnamed: D37.2 (A), K_37.2 (ROW)
unnamed: D38.2 (A), K_38.2 (ROW)
unnamed: D39.2 (A), K_39.2 (ROW)
unnamed: D40.2 (A), K_40.2 (ROW)
unnamed: D41.2 (A), K_41.2 (ROW)
unnamed: D42.2 (A), K_42.2 (ROW)
unnamed: D43.2 (A), K_43.2 (ROW)
unnamed: D44.2 (A), K_44.2 (ROW)
unnamed: D45.2 (A), K_45.2 (ROW)
unnamed: D46.2 (A), K_46.2 (ROW)
unnamed: D47.2 (A), K_47.2 (ROW)
unnamed: D48.2 (A), K_48.2 (ROW)
unnamed: D49.2 (A), K_49.2 (ROW)
unnamed: D50.2 (A), K_50.2 (ROW)
unnamed: D51.2 (A), K_51.2 (ROW)
unnamed: D52.2 (A), K_52.2 (ROW)
unnamed: D53.2 (A), K_53.2 (ROW)
unnamed: D54.2 (A), K_54.2 (ROW)
unnamed: D55.2 (A), K_55.2 (ROW)
unnamed: D56.2 (A), K_56.2 (ROW)
unnamed: D57.2 (A), K_57.2 (ROW)
unnamed: D58.2 (A), K_58.2 (ROW)
unnamed: D59.2 (A), K_59.2 (ROW)
unnamed: D60.2 (A), K_60.2 (ROW)
unnamed: D61.2 (A), K_61.2 (ROW)
unnamed: D62.2 (A), K_62.2 (ROW)
unnamed: D63.2 (A), K_63.2 (ROW), K_63B1.2 (ROW)
unnamed: D64.2 (A), K_64.2 (ROW), K_64B1.2 (ROW)
unnamed: D65.2 (A), K_65.2 (ROW)
unnamed: D66.2 (A), K_66.2 (ROW)
unnamed: D67.2 (A), K_67.2 (ROW)
unnamed: D68.2 (A), K_68.2 (ROW)
unnamed: D69.2 (A), K_69.2 (ROW)
unnamed: D70.2 (A), K_70.2 (ROW)
unnamed: D71.2 (A), K_71.2 (ROW)
unnamed: D72.2 (A), K_72.2 (ROW)
unnamed: D73.2 (A), K_73.2 (ROW)
unnamed: D74.2 (A), K_74.2 (ROW)
unnamed: D75.2 (A), K_75.2 (ROW)
unnamed: D76.2 (A), K_76.2 (ROW)
unnamed: D77.2 (A), K_77.2 (ROW)
unnamed: D78.2 (A), K_78.2 (ROW)
unnamed: D79.2 (A), K_79.2 (ROW)
unnamed: D80.2 (A), K_80.2 (ROW)
unnamed: D81.2 (A), K_81.2 (ROW)
unnamed: D82.2 (A), K_82.2 (ROW)
unnamed: D83.2 (A), K_83.2 (ROW)
unnamed: D84.2 (A), K_84.2 (ROW)
unnamed: D85.2 (A), K_85.2 (ROW)
unnamed: D86.2 (A), K_86.2 (ROW)
unnamed: D87.2 (A), K_87.2 (ROW)
unnamed: D88.2 (A), K_88.2 (ROW)
unnamed: LEDRESISTOR1.2, PowerLED0.2 (A)
unnamed: RESISTOR0.1, USB1.A5 (CC1)
unnamed: RESISTOR1.2, USB1.B5 (CC2)
USB2_N: RPI0.TP2 (USB_DM), USB1.A7 (D-), USB1.B7 (D-)
USB2_P: RPI0.TP3 (USB_DP), USB1.A6 (D+), USB1.B6 (D+)
USBVBUS: D89.2 (A), LEDRESISTOR1.1, USB1.A4 (VBUS), USB1.A9 (VBUS), USB1.B4 (VBUS), USB1.B9 (VBUS)
VSYS: D89.1 (K), RPI0.39 (VSYS)
col0: K_0.1 (COL), K_16.1 (COL), K_33.1 (COL), K_50.1 (COL), K_64.1 (COL), K_64B1.1 (COL), K_78.1 (COL), RPI0.4 (GPIO2)
col1: K_17.1 (COL), K_65.1 (COL), K_79.1 (COL), RPI0.5 (GPIO3)
col2: K_1.1 (COL), K_18.1 (COL), K_34.1 (COL), K_51.1 (COL), K_66.1 (COL), RPI0.6 (GPIO4)
col3: K_2.1 (COL), K_19.1 (COL), K_35.1 (COL), K_52.1 (COL), K_67.1 (COL), K_80.1 (COL), RPI0.7 (GPIO5)
col4: K_3.1 (COL), K_20.1 (COL), K_36.1 (COL), K_53.1 (COL), K_68.1 (COL), RPI0.9 (GPIO6)
col5: K_4.1 (COL), K_21.1 (COL), K_37.1 (COL), K_54.1 (COL), K_69.1 (COL), RPI0.10 (GPIO7)
col6: K_22.1 (COL), K_38.1 (COL), K_55.1 (COL), K_70.1 (COL), K_81.1 (COL), RPI0.11 (GPIO8)
col7: K_5.1 (COL), K_23.1 (COL), K_39.1 (COL), K_56.1 (COL), K_71.1 (COL), RPI0.12 (GPIO9)
col8: K_6.1 (COL), K_24.1 (COL), K_40.1 (COL), K_57.1 (COL), K_72.1 (COL), RPI0.14 (GPIO10)
col9: K_7.1 (COL), K_25.1 (COL), K_41.1 (COL), K_58.1 (COL), K_73.1 (COL), RPI0.15 (GPIO11)
col10: K_8.1 (COL), K_26.1 (COL), K_42.1 (COL), K_59.1 (COL), K_74.1 (COL), K_82.1 (COL), RPI0.16 (GPIO12)
col11: K_9.1 (COL), K_27.1 (COL), K_43.1 (COL), K_60.1 (COL), K_75.1 (COL), K_83.1 (COL), RPI0.17 (GPIO13)
col12: K_10.1 (COL), K_28.1 (COL), K_44.1 (COL), K_61.1 (COL), RPI0.19 (GPIO14)
col13: K_11.1 (COL), K_45.1 (COL), K_62.1 (COL), K_76.1 (COL), K_84.1 (COL), RPI0.20 (GPIO15)
col14: K_12.1 (COL), K_29.1 (COL), K_46.1 (COL), K_63.1 (COL), K_63B1.1 (COL), K_85.1 (COL), RPI0.25 (GPIO19)
col15: K_13.1 (COL), K_30.1 (COL), K_47.1 (COL), K_86.1 (COL), RPI0.24 (GPIO18)
col16: K_14.1 (COL), K_31.1 (COL), K_48.1 (COL), K_77.1 (COL), K_87.1 (COL), RPI0.22 (GPIO17)
col17: K_15.1 (COL), K_32.1 (COL), K_49.1 (COL), K_88.1 (COL), RPI0.21 (GPIO16)
row0: D0.1 (K), D1.1 (K), D2.1 (K), D3.1 (K), D4.1 (K), D5.1 (K), D6.1 (K), D7.1 (K), D8.1 (K), D9.1 (K), D10.1 (K), D11.1 (K), D12.1 (K), D13.1 (K), D14.1 (K), D15.1 (K), RPI0.26 (GPIO20)
row2: D16.1 (K), D17.1 (K), D18.1 (K), D19.1 (K), D20.1 (K), D21.1 (K), D22.1 (K), D23.1 (K), D24.1 (K), D25.1 (K), D26.1 (K), D27.1 (K), D28.1 (K), D29.1 (K), D30.1 (K), D31.1 (K), D32.1 (K), RPI0.27 (GPIO21)
row3: D33.1 (K), D34.1 (K), D35.1 (K), D36.1 (K), D37.1 (K), D38.1 (K), D39.1 (K), D40.1 (K), D41.1 (K), D42.1 (K), D43.1 (K), D44.1 (K), D45.1 (K), D46.1 (K), D47.1 (K), D48.1 (K), D49.1 (K), RPI0.29 (GPIO22)
row4: D50.1 (K), D51.1 (K), D52.1 (K), D53.1 (K), D54.1 (K), D55.1 (K), D56.1 (K), D57.1 (K), D58.1 (K), D59.1 (K), D60.1 (K), D61.1 (K), D62.1 (K), D63.1 (K), RPI0.31 (GPIO26_ADC0)
row5: D64.1 (K), D65.1 (K), D66.1 (K), D67.1 (K), D68.1 (K), D69.1 (K), D70.1 (K), D71.1 (K), D72.1 (K), D73.1 (K), D74.1 (K), D75.1 (K), D76.1 (K), D77.1 (K), RPI0.32 (GPIO27_ADC1)
row6: D78.1 (K), D79.1 (K), D80.1 (K), D81.1 (K), D82.1 (K), D83.1 (K), D84.1 (K), D85.1 (K), D86.1 (K), D87.1 (K), D88.1 (K), RPI0.34 (GPIO28_ADC2)

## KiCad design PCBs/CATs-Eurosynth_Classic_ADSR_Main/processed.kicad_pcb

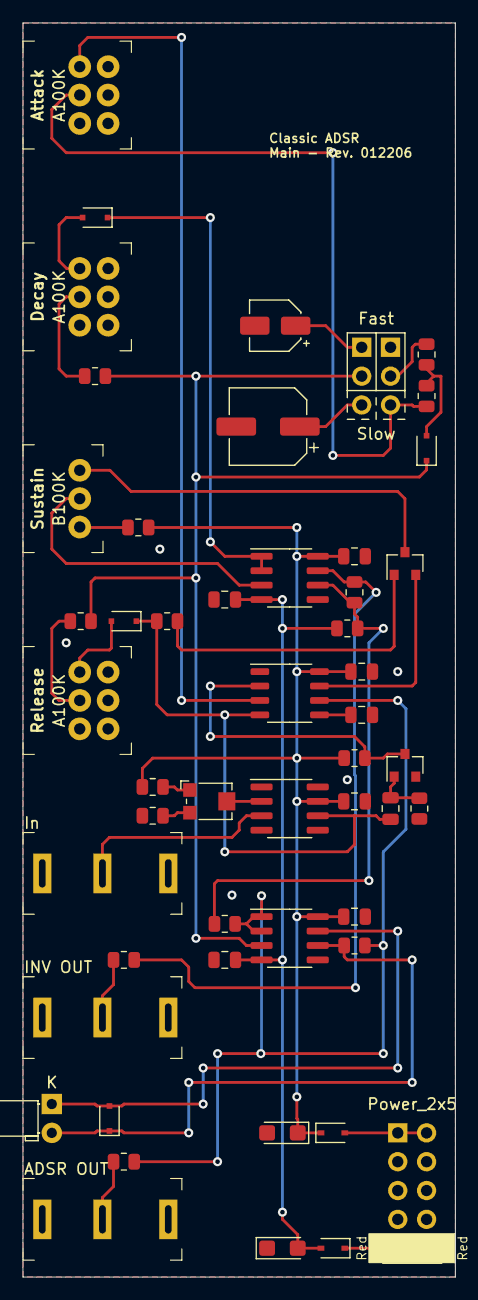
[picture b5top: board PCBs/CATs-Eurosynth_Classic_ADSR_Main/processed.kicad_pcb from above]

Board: 2 copper layers, 38.1 x 110.5 mm, 52 parts (0 on the bottom side), 37 nets.

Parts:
C1, C2, C4, C5, C6, C10: 100n; C_0805_2012Metric
C3, C7: 10n; C_0805_2012Metric
C8: 100µ; CP_Elec_6.3x5.4
C9: 10µ; CP_Elec_4x5.4
C11, C12: 10µF; CP_EIA-3216-18_Kemet-A
D1, D2: 1N5819WS; D_SOD-323
D3, D4, D5, D6: 1N4148WS; D_SOD-323F
D7: LED; LED_D3.0mm_Horizontal_O1.27mm_Z6.0mm
J1: In; Jack_3.5mm_QingPu_WQP-PJ323M
J2: Power_2x5; Power_2x5_Vertical
J3: ADSR OUT; Jack_3.5mm_QingPu_WQP-PJ323M
J4: INV OUT; Jack_3.5mm_QingPu_WQP-PJ323M
JP1, JP2: SLOW/FAST; PinHeader_1x03_P2.54mm_Vertical
P1: B100K; Potentiometer_AlpsAlpine_RK0971110
P2, P3, P4: A100K; Potentiometer_AlpsAlpine_RK09712200_Solo
Q1: MMBT3904; SOT-23
Q2: 2N7002; SOT-23
R1: 27k; R_0805_2012Metric
R2: 10k; R_0805_2012Metric
R3, R4: 22k; R_0805_2012Metric
R5: 1M; R_0805_2012Metric
R6: 4.7k; R_0805_2012Metric
R7, R10: 100; R_0805_2012Metric
R8: 680; R_0805_2012Metric
R9: 120; R_0805_2012Metric
R11: 120k; R_0805_2012Metric
R12, R15: 100k; R_0805_2012Metric
R13, R16: 1k; R_0805_2012Metric
R14: 2.4k; R_0805_2012Metric
T1: 20k; Potentiometer_Bourns_TC33X_Vertical
U1: OP07; SOIC-8_3.9x4.9mm_P1.27mm
U2, U3: TL072; SOIC-8_3.9x4.9mm_P1.27mm
U4: ICM7555xB; SOP-8_3.9x4.9mm_P1.27mm

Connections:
+12V: C1.2, C4.2, C6.2, C10.2, C11.1, D1.1, R1.1, R4.1, R6.1, U1.7, U2.8, U3.8, U4.8
-12V: C2.1, C5.1, C12.2, D2.2, R11.2, U2.4, U3.4
GND: C1.1, C2.2, C4.1, C5.2, C6.1, C7.1, C8.2, C9.2, C10.1, C11.2, C12.1, J1.S, J1.TN, J2.GND, J3.S, J4.S, Q1.2, R2.2, R3.2, U1.4, U2.5, U3.5, U4.1
unnamed: C3.1, Q1.1, R3.1
unnamed: C3.2, D4.1, R5.2, U1.6, U4.4
unnamed: C7.2, U4.5
unnamed: C8.1, JP2.3
unnamed: C9.1, JP2.1
unnamed: D1.2, J2.+12V
unnamed: D2.1, J2.-12V
unnamed: D3.1, U2.1, U2.2
unnamed: D3.2, P3.CCW
unnamed: D4.2, P4.CCW
unnamed: D5.1, JP2.2, R7.1, R10.1, U3.3
unnamed: D5.2, R8.1, R9.1
unnamed: D6.1, D7.2, R14.1, U3.6
unnamed: D6.2, D7.1, U3.7
unnamed: J1.T, U1.3
unnamed: J3.T, R13.1
unnamed: J4.T, R16.1
unnamed: JP1.2, R9.2
unnamed: JP1.3, P2.W, R8.2
unnamed: P1.CCW, Q2.3
unnamed: P1.CW, R6.2
unnamed: P1.W, U2.3
unnamed: P2.CCW, U4.3
unnamed: P3.W, R7.2
unnamed: P4.W, R10.2
unnamed: Q1.3, R4.2, U4.2
unnamed: Q2.1, R5.1
unnamed: Q2.2, U4.7
unnamed: R1.2, T1.1
unnamed: R2.1, T1.3
unnamed: R11.1, R12.2, R15.1, U2.6
unnamed: R12.1, R13.2, R14.2, U3.1, U3.2, U4.6
unnamed: R15.2, R16.2, U2.7
unnamed: T1.2, U1.2
